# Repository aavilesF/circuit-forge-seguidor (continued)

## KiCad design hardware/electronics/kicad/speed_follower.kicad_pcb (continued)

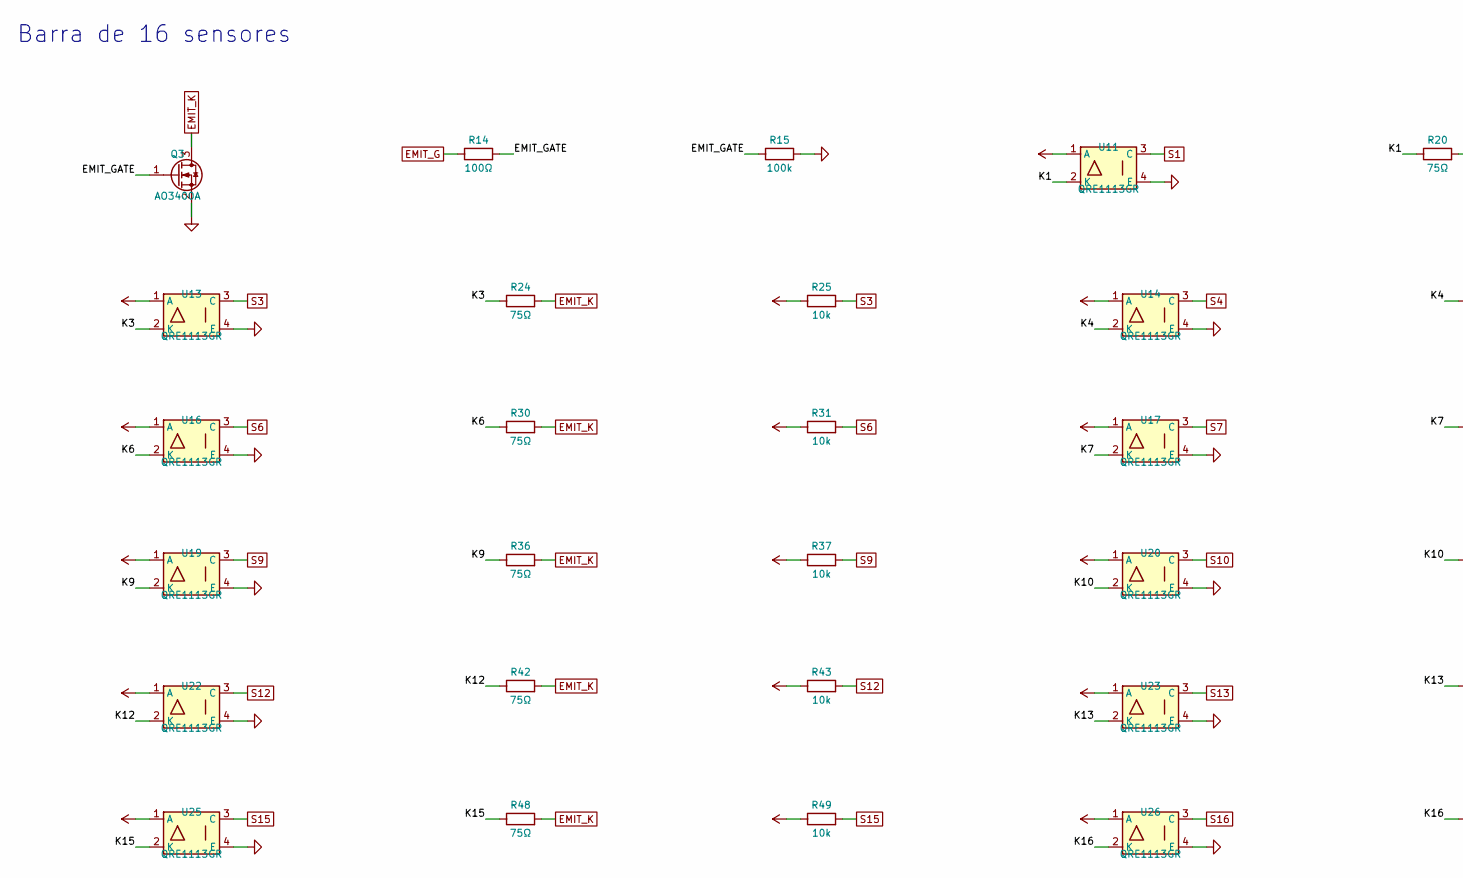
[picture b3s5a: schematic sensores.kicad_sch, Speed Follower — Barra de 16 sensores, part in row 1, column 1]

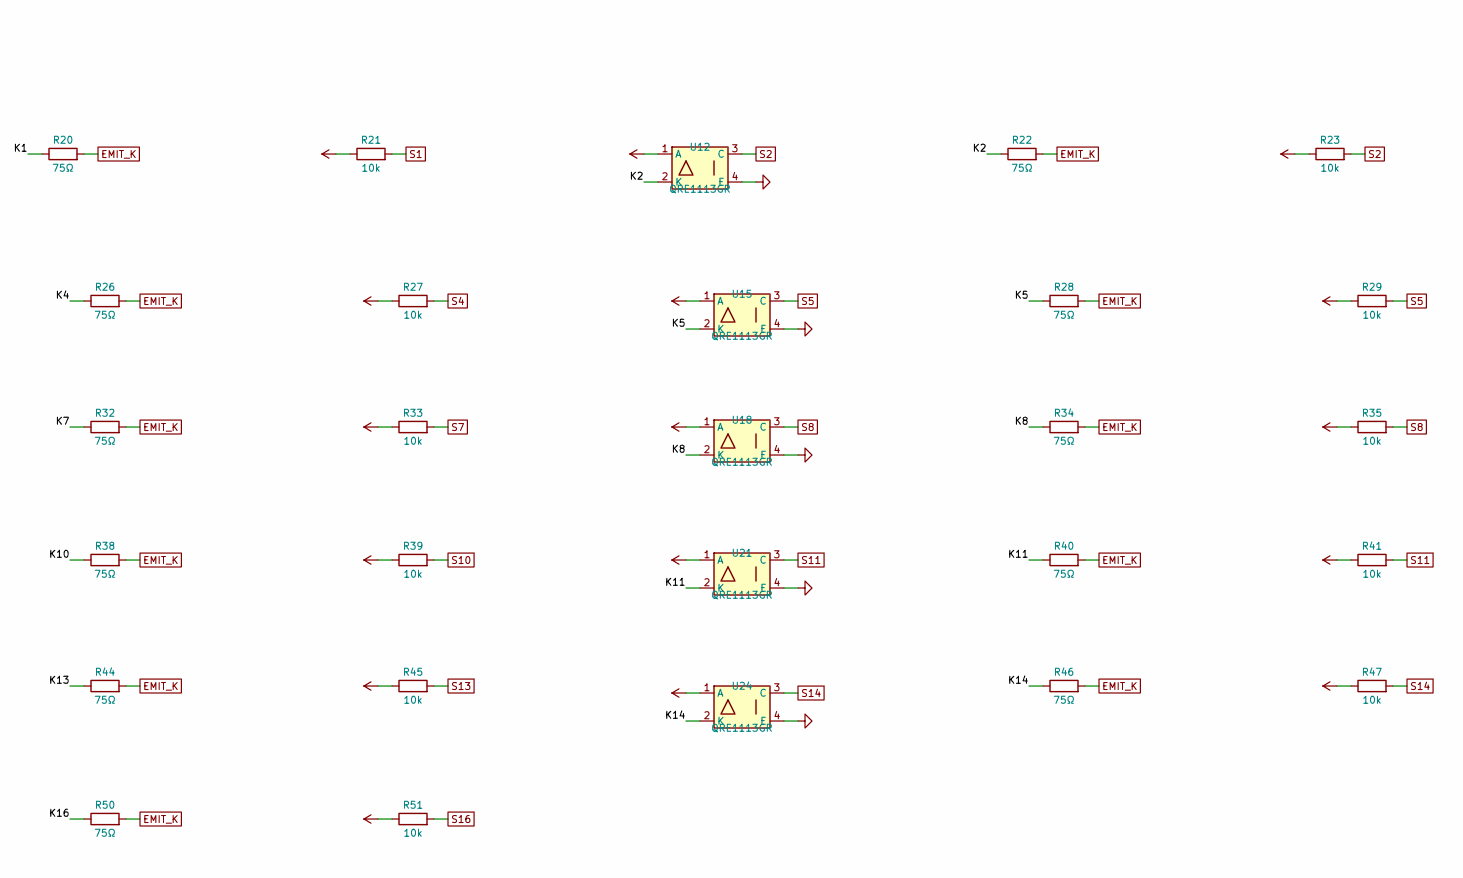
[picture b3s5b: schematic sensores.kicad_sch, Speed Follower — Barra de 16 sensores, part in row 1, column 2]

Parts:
Q3: AO3400A; SOT-23; MPN AO3400A
R14: 100Ω; R_0402_1005Metric; MPN RC0402FR-07100RL
R15: 100k; R_0402_1005Metric; MPN RC0402FR-07100KL
R20, R22, R24, R26, R28, R30, R32, R34, R36, R38, R40, R42, R44, R46, R48, R50: 75Ω; R_0603_1608Metric; MPN RC0603FR-0775RL
R21, R23, R25, R27, R29, R31, R33, R35, R37, R39, R41, R43, R45, R47, R49, R51: 10k; R_0402_1005Metric; MPN RC0402FR-0710KL
U11, U12, U13, U14, U15, U16, U17, U18, U19, U20, U21, U22, U23, U24, U25, U26: QRE1113GR; OnSemi_CASE100CY; MPN QRE1113GR

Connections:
+3V3: R21.1, R23.1, R25.1, R27.1, R29.1, R31.1, R33.1, R35.1, R37.1, R39.1, R41.1, R43.1, R45.1, R47.1, R49.1, R51.1, U11.1 (A), U12.1 (A), U13.1 (A), U14.1 (A), U15.1 (A), U16.1 (A), U17.1 (A), U18.1 (A), U19.1 (A), U20.1 (A), U21.1 (A), U22.1 (A), U23.1 (A), U24.1 (A), U25.1 (A), U26.1 (A); also elsewhere on the board
/Barra de 16 sensores/EMIT_GATE: Q3.1 (G), R14.2, R15.1
/Barra de 16 sensores/K1: R20.1, U11.2 (K)
/Barra de 16 sensores/K2: R22.1, U12.2 (K)
/Barra de 16 sensores/K3: R24.1, U13.2 (K)
/Barra de 16 sensores/K4: R26.1, U14.2 (K)
/Barra de 16 sensores/K5: R28.1, U15.2 (K)
/Barra de 16 sensores/K6: R30.1, U16.2 (K)
/Barra de 16 sensores/K7: R32.1, U17.2 (K)
/Barra de 16 sensores/K8: R34.1, U18.2 (K)
/Barra de 16 sensores/K9: R36.1, U19.2 (K)
/Barra de 16 sensores/K10: R38.1, U20.2 (K)
/Barra de 16 sensores/K11: R40.1, U21.2 (K)
/Barra de 16 sensores/K12: R42.1, U22.2 (K)
/Barra de 16 sensores/K13: R44.1, U23.2 (K)
/Barra de 16 sensores/K14: R46.1, U24.2 (K)
/Barra de 16 sensores/K15: R48.1, U25.2 (K)
/Barra de 16 sensores/K16: R50.1, U26.2 (K)
EMIT_G: R14.1; also elsewhere on the board
EMIT_K: Q3.3 (D), R20.2, R22.2, R24.2, R26.2, R28.2, R30.2, R32.2, R34.2, R36.2, R38.2, R40.2, R42.2, R44.2, R46.2, R48.2, R50.2; also elsewhere on the board
GND: Q3.2 (S), R15.2, U11.4 (E), U12.4 (E), U13.4 (E), U14.4 (E), U15.4 (E), U16.4 (E), U17.4 (E), U18.4 (E), U19.4 (E), U20.4 (E), U21.4 (E), U22.4 (E), U23.4 (E), U24.4 (E), U25.4 (E), U26.4 (E); also elsewhere on the board
S1: R21.2, U11.3 (C); also elsewhere on the board
S2: R23.2, U12.3 (C); also elsewhere on the board
S3: R25.2, U13.3 (C); also elsewhere on the board
S4: R27.2, U14.3 (C); also elsewhere on the board
S5: R29.2, U15.3 (C); also elsewhere on the board
S6: R31.2, U16.3 (C); also elsewhere on the board
S7: R33.2, U17.3 (C); also elsewhere on the board
S8: R35.2, U18.3 (C); also elsewhere on the board
S9: R37.2, U19.3 (C); also elsewhere on the board
S10: R39.2, U20.3 (C); also elsewhere on the board
S11: R41.2, U21.3 (C); also elsewhere on the board
S12: R43.2, U22.3 (C); also elsewhere on the board
S13: R45.2, U23.3 (C); also elsewhere on the board
S14: R47.2, U24.3 (C); also elsewhere on the board
S15: R49.2, U25.3 (C); also elsewhere on the board
S16: R51.2, U26.3 (C); also elsewhere on the board

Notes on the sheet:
Barra de 16 sensores

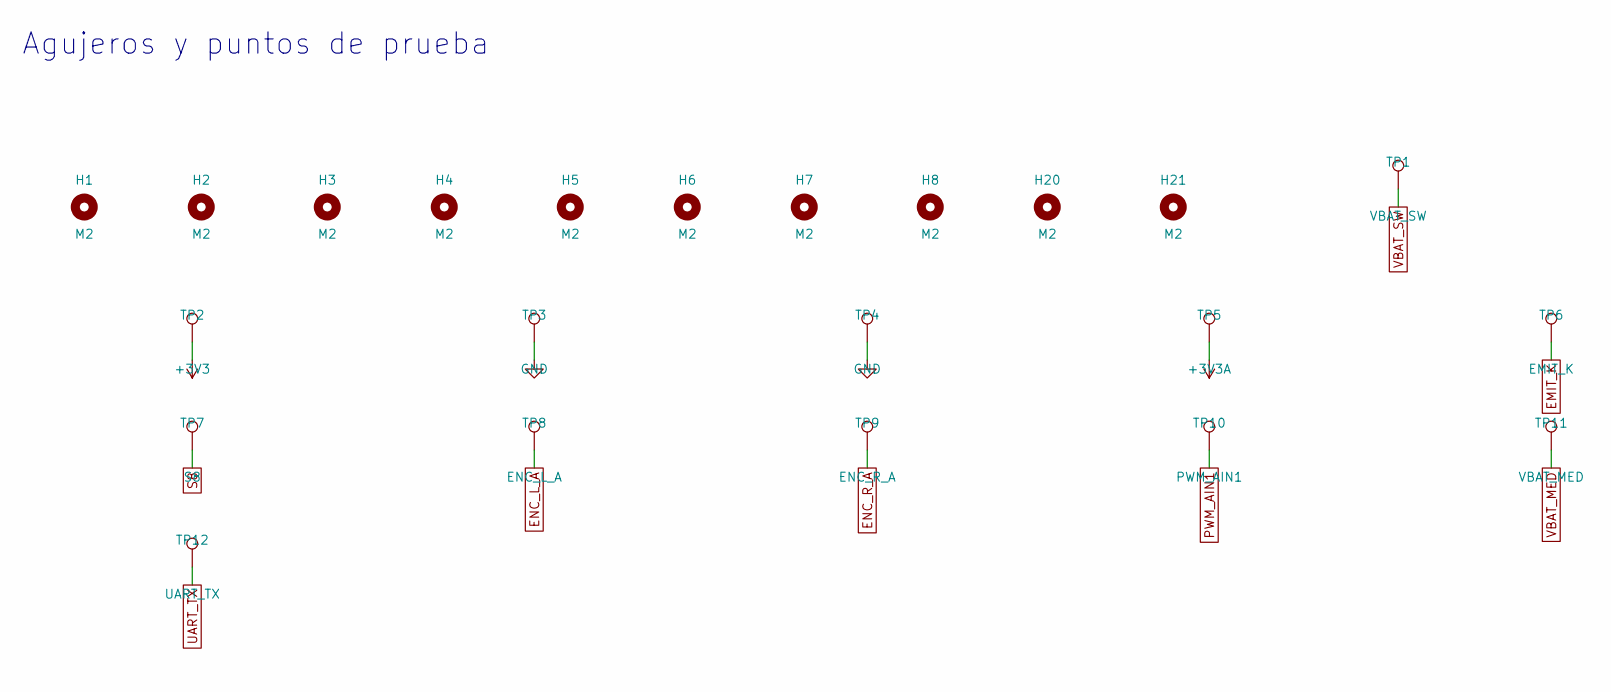
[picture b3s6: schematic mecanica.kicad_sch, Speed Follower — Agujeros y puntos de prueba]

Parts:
H1, H2, H3, H4, H5, H6, H7, H8, H20, H21: M2; MountingHole_2.2mm_M2; MPN —
TP1: VBAT_SW; TestPoint_Pad_D1.0mm; MPN —
TP2: +3V3; TestPoint_Pad_D1.0mm; MPN —
TP3, TP4: GND; TestPoint_Pad_D1.0mm; MPN —
TP5: +3V3A; TestPoint_Pad_D1.0mm; MPN —
TP6: EMIT_K; TestPoint_Pad_D1.0mm; MPN —
TP7: S8; TestPoint_Pad_D1.0mm; MPN —
TP8: ENC_L_A; TestPoint_Pad_D1.0mm; MPN —
TP9: ENC_R_A; TestPoint_Pad_D1.0mm; MPN —
TP10: PWM_AIN1; TestPoint_Pad_D1.0mm; MPN —
TP11: VBAT_MED; TestPoint_Pad_D1.0mm; MPN —
TP12: UART_TX; TestPoint_Pad_D1.0mm; MPN —

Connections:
+3V3: TP2.1; also elsewhere on the board
+3V3A: TP5.1; also elsewhere on the board
EMIT_K: TP6.1; also elsewhere on the board
ENC_L_A: TP8.1; also elsewhere on the board
ENC_R_A: TP9.1; also elsewhere on the board
GND: TP3.1, TP4.1; also elsewhere on the board
PWM_AIN1: TP10.1; also elsewhere on the board
S8: TP7.1; also elsewhere on the board
UART_TX: TP12.1; also elsewhere on the board
VBAT_MED: TP11.1; also elsewhere on the board
VBAT_SW: TP1.1; also elsewhere on the board

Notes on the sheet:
Agujeros y puntos de prueba

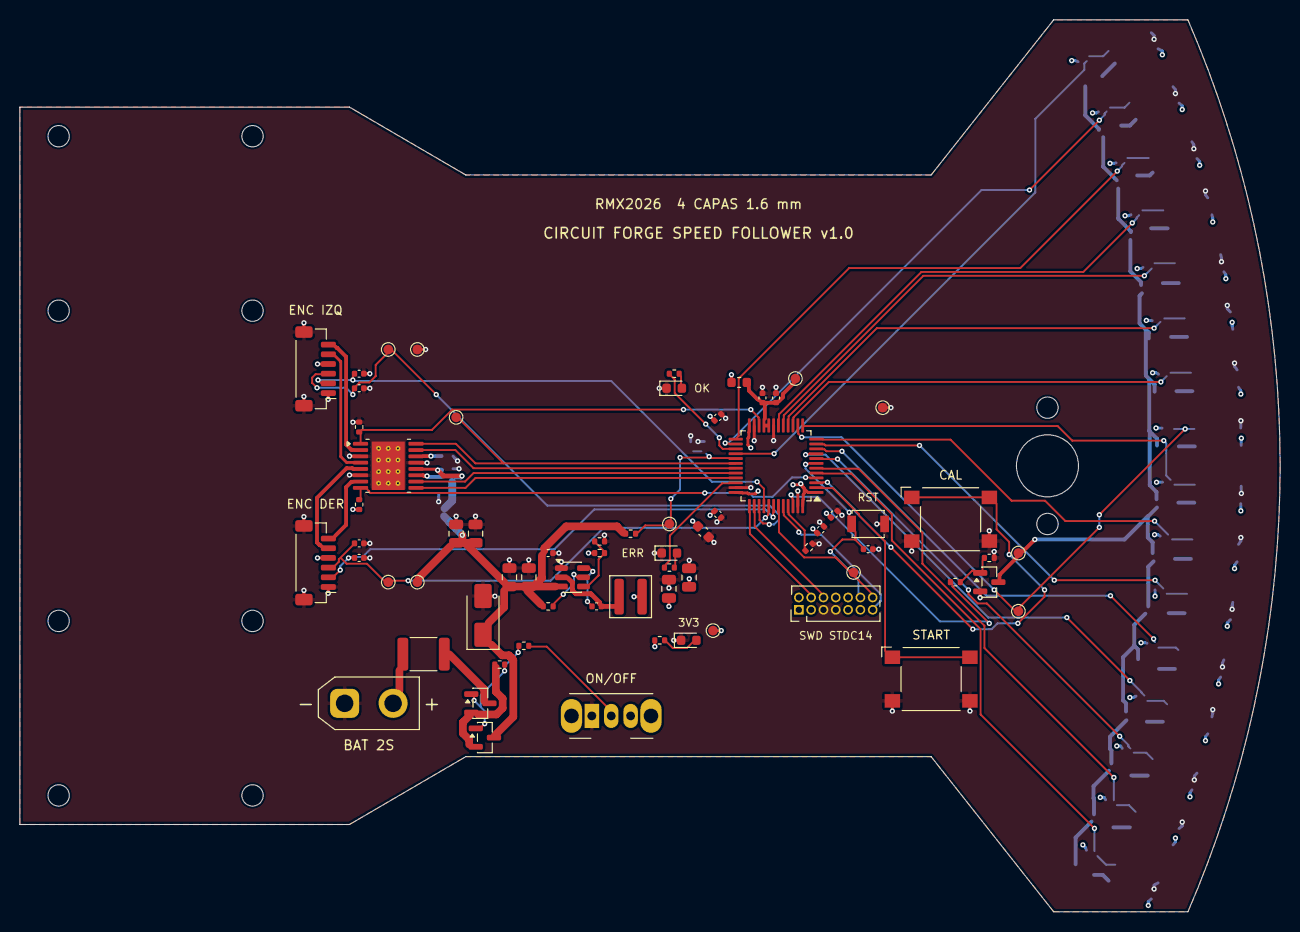
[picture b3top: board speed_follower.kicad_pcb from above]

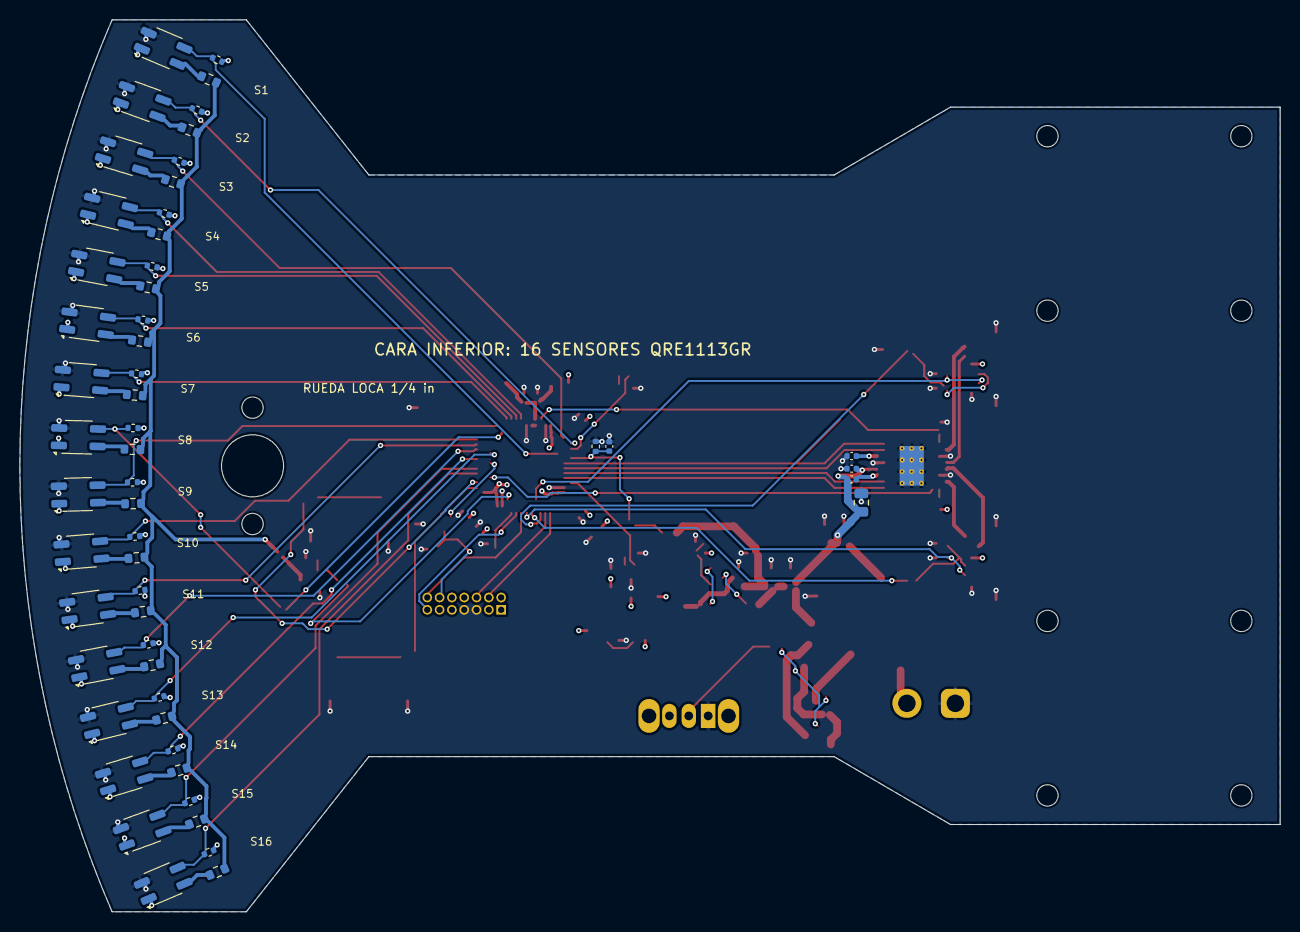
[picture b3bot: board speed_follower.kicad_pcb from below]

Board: 4 copper layers, 130.0 x 92.0 mm, 131 parts (54 on the bottom side), 78 nets.

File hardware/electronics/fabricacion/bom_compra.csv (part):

categoria,fabricante,modelo,numero_parte,descripcion,cantidad,tension,corriente,dimensiones,masa_unitaria_g,encapsulado,footprint,funcion,datasheet,observaciones_montaje,referencias,lado,verificado
A,Changzhou Amass Electronics,XT30UPB-M,XT30UPB-M,"Conector de batería XT30 macho vertical para PCB, 15 A (pin 1 −, pin 2 +)",1,500 V,15 A (30 A pico),10.2 × 5.2 × 8 mm (APROX),1.5,THT vertical,Connector_AMASS:AMASS_XT30UPB-M_1x02_P5.0mm_Vertical,Conector de batería (macho),https://www.tme.eu/Document/e5863b891432488e7531b3c4468225ac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,Verificar que el paquete Tattu traiga XT30 hembra (XT30U-F) antes de soldar,J1,superior,lcsc.com C428721; huella oficial KiCad AMASS
A,Littelfuse,1.5A/12V,1812L150/12DR,"Fusible reajustable PTC 1812, Ihold 1.5 A, 12 V",1,12 V máx,Ihold 1.5 A,4.5 × 3.2 mm,0.05,1812,Fuse:Fuse_1812_4532Metric,Fusible reajustable de la batería,https://www.littelfuse.com/assetdocs/littelfuse-ptc-1812l-datasheet,,F1,superior,digikey.com 1812L150-12DR
A,Alpha & Omega Semiconductor,AO3401A,AO3401A,MOSFET P −30 V −4 A SOT-23 (protección contra inversión),2,"VDS −30 V, VGS ±12 V",−4 A,2.9 × 1.3 × 1.1 mm,0.008,SOT-23,Package_TO_SOT_SMD:SOT-23,MOSFET P: inversión de polaridad y encendido,https://www.aosmd.com/res/datasheets/AO3401A.pdf,Q1 y Q2 espalda con espalda (fuentes unidas),Q1 Q2,superior,aosmd.com / distribuidores
A,YAGEO,100k,RC0402FR-07100KL,Resistencia 100kΩ 1 % 0402,5,50 V,1/16 W,1.0 × 0.5 mm,0.0006,0402,Resistor_SMD:R_0402_1005Metric,Resistencia,https://www.yageo.com/upload/media/product/productsearch/dat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,,R1 R3 R5 R13 R15,superior,nomenclatura de catálogo YAGEO RC (RC0402FR-07xxxL / RC0603FR-07xxxL)
A,YAGEO,10k,RC0402FR-0710KL,Resistencia 10kΩ 1 % 0402,20,50 V,1/16 W,1.0 × 0.5 mm,0.0006,0402,Resistor_SMD:R_0402_1005Metric,Resistencia,https://www.yageo.com/upload/media/product/productsearch/dat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,,R2 R7 R9 R12 R21 R23 R25 R27 R29 R31 R33 R35 R37 R39 R41 R43 R45 R47 R49 R51,inferior / superior,nomenclatura de catálogo YAGEO RC (RC0402FR-07xxxL / RC0603FR-07xxxL)
A,C&K,ENCENDIDO,OS102011MA1QN1,"Interruptor deslizante SPDT de ángulo recto, 100 mA 12 V (solo conmuta la compuerta)",1,12 V DC,100 mA,8.6 × 4.4 mm (cuerpo),0.5,THT ángulo recto,Button_Switch_THT:SW_Slide_SPDT_Angled_CK_OS102011MA1Q,Interruptor de encendido (conmuta la compuerta de Q1/Q2),https://www.ckswitches.com/media/1428/os.pdf,Actuador hacia el borde derecho,SW1,superior,rs-online 7874855; digikey OS102011MA1QN1
A,Littelfuse,SMAJ9.0A,SMAJ9.0A,"TVS unidireccional 400 W, 9.0 V de trabajo (DO-214AC)",1,"VRWM 9.0 V, Vc 15.4 V",26 A pico,4.3 × 2.6 × 2.2 mm,0.07,DO-214AC (SMA),Diode_SMD:D_SMA,TVS de la alimentación del motor,https://www.littelfuse.com/assetdocs/littelfuse-tvs-diode-sm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,Cátodo (banda) hacia VBAT_SW,D1,superior,digikey.com SMAJ9-0A (Littelfuse)
A,Murata,22µF,GRM21BR61E226ME44L,Condensador cerámico 22µF 25 V X5R 0805,4,25 V,,2.0 × 1.25 mm,0.008,0805,Capacitor_SMD:C_0805_2012Metric,Condensador,https://www.murata.com/en-us/products/capacitor/ceramiccapacitor,,C1 C2 C8 C9,superior,distribuidores (Murata GRM)
A,YAGEO,33k,RC0402FR-0733KL,Resistencia 33kΩ 1 % 0402,1,50 V,1/16 W,1.0 × 0.5 mm,0.0006,0402,Resistor_SMD:R_0402_1005Metric,Resistencia,https://www.yageo.com/upload/media/product/productsearch/dat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,,R4,inferior,nomenclatura de catálogo YAGEO RC (RC0402FR-07xxxL / RC0603FR-07xxxL)
A,Murata,100nF,GRM155R71C104KA88D,Condensador cerámico 100nF 16 V X7R 0402,10,16 V,,1.0 × 0.5 mm,0.0006,0402,Capacitor_SMD:C_0402_1005Metric,Condensador,https://www.murata.com/en-us/products/capacitor/ceramiccapacitor,,C3 C6 C7 C10 C11 C12 C13 C16 C17 C21,inferior / superior,distribuidores (Murata GRM)
A,Texas Instruments,TPS563200,TPS563200DDCR,"Convertidor reductor síncrono 4.5-17 V, 3 A, 650 kHz (SOT-23-6)",1,VIN 4.5-17 V,3 A,2.9 × 1.6 × 1.1 mm,0.02,SOT-23-6,Package_TO_SOT_SMD:SOT-23-6,Reductor 3.3 V,https://www.ti.com/lit/ds/symlink/tps563200.pdf,R6/R7 fijan 3.30 V (VFB 0.765 V),U2,superior,pines y tabla de componentes: hoja de datos TI (chipdip.ru DOC003725965)
A,Murata,10µF,GRM21BR61E106KA73L,Condensador cerámico 10µF 25 V X5R 0805,3,25 V,,2.0 × 1.25 mm,0.008,0805,Capacitor_SMD:C_0805_2012Metric,Condensador,https://www.murata.com/en-us/products/capacitor/ceramiccapacitor,,C4 C5 C20,inferior / superior,distribuidores (Murata GRM)
A,Würth Elektronik,2.2µH,74438357022,"Inductor blindado WE-MAPI 4030, 2.2 µH, IR 7.1 A, Isat 9.2 A, 26 mΩ",1,—,"IR 7.1 A, Isat 9.2 A",4.1 × 4.1 × 3.1 mm,0.25,WE-MAPI 4030,Inductor_SMD:L_Wuerth_MAPI-4030,Inductor del reductor,https://www.we-online.com/components/products/datasheet/7443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,,L1,superior,"digikey.com / flux.ai (WE-MAPI 4030, 2.2 µH, 26 mΩ)"
A,YAGEO,33.2k,RC0402FR-0733K2L,Resistencia 33.2kΩ 1 % 0402,1,50 V,1/16 W,1.0 × 0.5 mm,0.0006,0402,Resistor_SMD:R_0402_1005Metric,Resistencia,https://www.yageo.com/upload/media/product/productsearch/dat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,,R6,superior,nomenclatura de catálogo YAGEO RC (RC0402FR-07xxxL / RC0603FR-07xxxL)
A,Kingbright,PWR,APT1608SGC,LED verde 0603 (3.3 V presente),2,VF ≈ 2.2 V,20 mA máx,1.6 × 0.8 mm,0.002,0603,LED_SMD:LED_0603_1608Metric,LED verde (3.3 V y estado),https://www.kingbrightusa.com/images/catalog/SPEC/APT1608SGC.pdf,Cátodo: marca verde/raya de la huella,D2 D3,superior,digikey APT1608SGC (Kingbright)
A,YAGEO,1k,RC0402FR-071KL,Resistencia 1kΩ 1 % 0402,3,50 V,1/16 W,1.0 × 0.5 mm,0.0006,0402,Resistor_SMD:R_0402_1005Metric,Resistencia,https://www.yageo.com/upload/media/product/productsearch/dat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,,R8 R10 R11,superior,nomenclatura de catálogo YAGEO RC (RC0402FR-07xxxL / RC0603FR-07xxxL)
A,STMicroelectronics,STM32G431CBT6,STM32G431CBT6,"MCU Arm Cortex-M4F 170 MHz, 128 KB flash, 32 KB RAM, 2 ADC 12 bits, LQFP-48",1,1.71-3.6 V,≈ 30 mA a 170 MHz,7 × 7 × 1.4 mm,0.2,LQFP-48,Package_QFP:LQFP-48_7x7mm_P0.5mm,"Microcontrolador (control, ADC, PWM, encoders)",https://www.st.com/resource/en/datasheet/stm32g431cb.pdf,"Pin 1 marcado en la serigrafía; soldar con flux, revisar puentes entre pines",U1,superior,ficha y pines: st.com; funciones alternas: STM32_open_pin_data (ST)
A,Murata,4.7µF,GRM188R61A475KE15D,Condensador cerámico 4.7µF 10 V X5R 0603,1,10 V,,1.6 × 0.8 mm,0.002,0603,Capacitor_SMD:C_0603_1608Metric,Condensador,https://www.murata.com/en-us/products/capacitor/ceramiccapacitor,,C14,superior,distribuidores (Murata GRM)
A,Murata,220Ω@100MHz,BLM18PG221SN1D,"Ferrita 220 Ω a 100 MHz, 1.4 A, 0603 (filtro de VDDA)",1,—,1.4 A,1.6 × 0.8 × 0.8 mm,0.003,0603,Inductor_SMD:L_0603_1608Metric,Ferrita de VDDA,https://www.murata.com/en-us/products/productdetail?partno=B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,,FB1,superior,digikey.com / rs-online
A,Murata,1µF,GRM155R61A105KE15D,Condensador cerámico 1µF 10 V X5R 0402,1,10 V,,1.0 × 0.5 mm,0.0006,0402,Capacitor_SMD:C_0402_1005Metric,Condensador,https://www.murata.com/en-us/products/capacitor/ceramiccapacitor,,C15,superior,distribuidores (Murata GRM)
A,Omron,RESET,B3U-1000P,Pulsador táctil SMD 3.0 × 2.5 mm (reinicio),1,12 V DC,50 mA,3.0 × 2.5 × 1.6 mm,0.03,SMD,Button_Switch_SMD:SW_SPST_B3U-1000P,Botón RESET,https://omronfs.omron.com/en_US/ecb/products/pdf/en-b3u.pdf,,SW4,superior,lcsc C231329; omron.com
A,Omron,START,B3FS-1000P,"Pulsador táctil SMD 6 × 6 × 3.1 mm (arranque, regla R08)",2,24 V DC,50 mA,6 × 6 × 3.1 mm,0.25,SMD,Button_Switch_SMD:SW_SPST_Omron_B3FS-100xP,Botones START y CAL,https://omronfs.omron.com/en_US/ecb/products/pdf/en-b3fs.pdf,,SW2 SW3,superior,lcsc C271750; omron.com
A,Kingbright,ERR,APT1608EC,LED rojo 0603 (falla / batería baja),1,VF ≈ 2.0 V,20 mA máx,1.6 × 0.8 mm,0.002,0603,LED_SMD:LED_0603_1608Metric,LED rojo (falla),https://www.kingbrightusa.com/images/catalog/SPEC/APT1608SGC.pdf,,D4,superior,digikey APT1608EC (Kingbright)
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
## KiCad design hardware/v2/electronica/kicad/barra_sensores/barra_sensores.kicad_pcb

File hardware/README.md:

# Hardware — Speed Follower (configuración definitiva)

| Carpeta | Contenido | Detalle |
|---|---|---|
| [`electronics/`](electronics/README.md) | Proyecto KiCad 9 (esquemático jerárquico y PCB-chasis de 4 capas ruteada), generadores, verificaciones ERC/DRC/paridad, paquete de fabricación y vistas 2D/3D de la PCBA | [`electronics/README.md`](electronics/README.md), [`electronics/fabricacion/LEEME.md`](electronics/fabricacion/LEEME.md) |
| [`mechanical/`](mechanical/README.md) | CAD del robot completo (CadQuery): piezas impresas en STEP/STL, planos, ensamble STEP, vistas, verificación de interferencias, caja, altura, masa y CG | [`mechanical/README.md`](mechanical/README.md), [`mechanical/VERIFICACION_MECANICA.md`](mechanical/VERIFICACION_MECANICA.md) |
| `geometria.py` | Geometría única del robot (contorno de la PCB, arco y posición de los sensores, soportes, rueda loca, alturas) calculada desde `config/robot_maestro.yaml`; la usan la PCB, el CAD y las verificaciones | — |

Arquitectura y justificación: [`docs/ARQUITECTURA.md`](../docs/ARQUITECTURA.md). Lista de compra: [`docs/BOM_FINAL.csv`](../docs/BOM_FINAL.csv).
Montaje, pruebas de aceptación y calibración: [`docs/MANUAL_ENSAMBLAJE.md`](../docs/MANUAL_ENSAMBLAJE.md).

Todo lo que contiene esta carpeta está verificado en **EDA y CAD**; no hay placa ni robot fabricados.

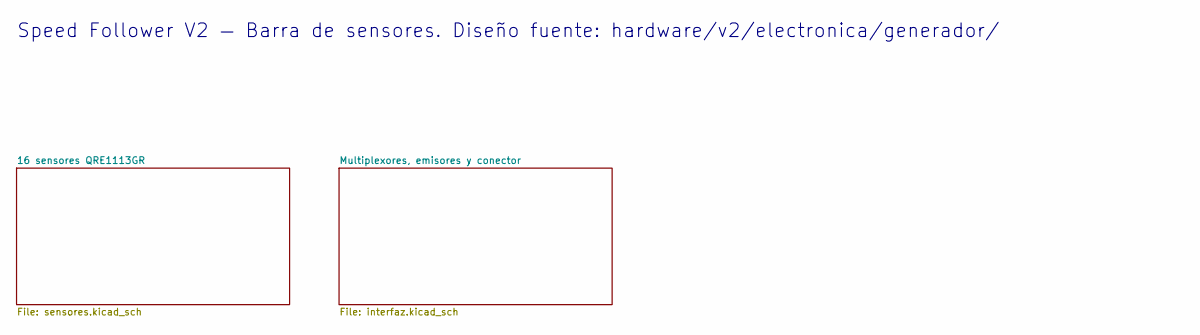
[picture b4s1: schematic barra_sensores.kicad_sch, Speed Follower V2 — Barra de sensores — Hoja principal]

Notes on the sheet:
Speed Follower V2 — Barra de sensores. Diseño fuente: hardware/v2/electronica/generador/

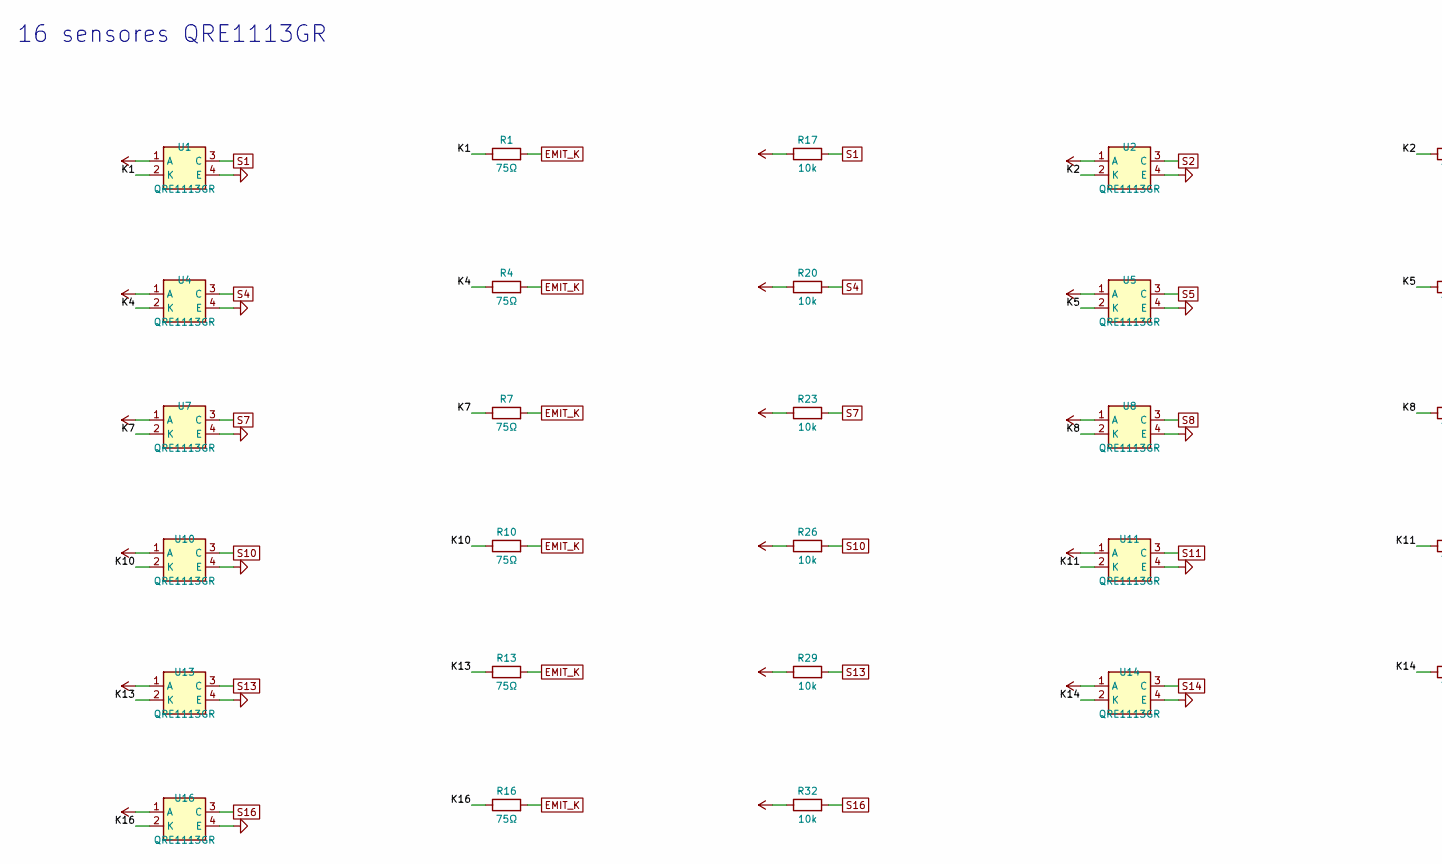
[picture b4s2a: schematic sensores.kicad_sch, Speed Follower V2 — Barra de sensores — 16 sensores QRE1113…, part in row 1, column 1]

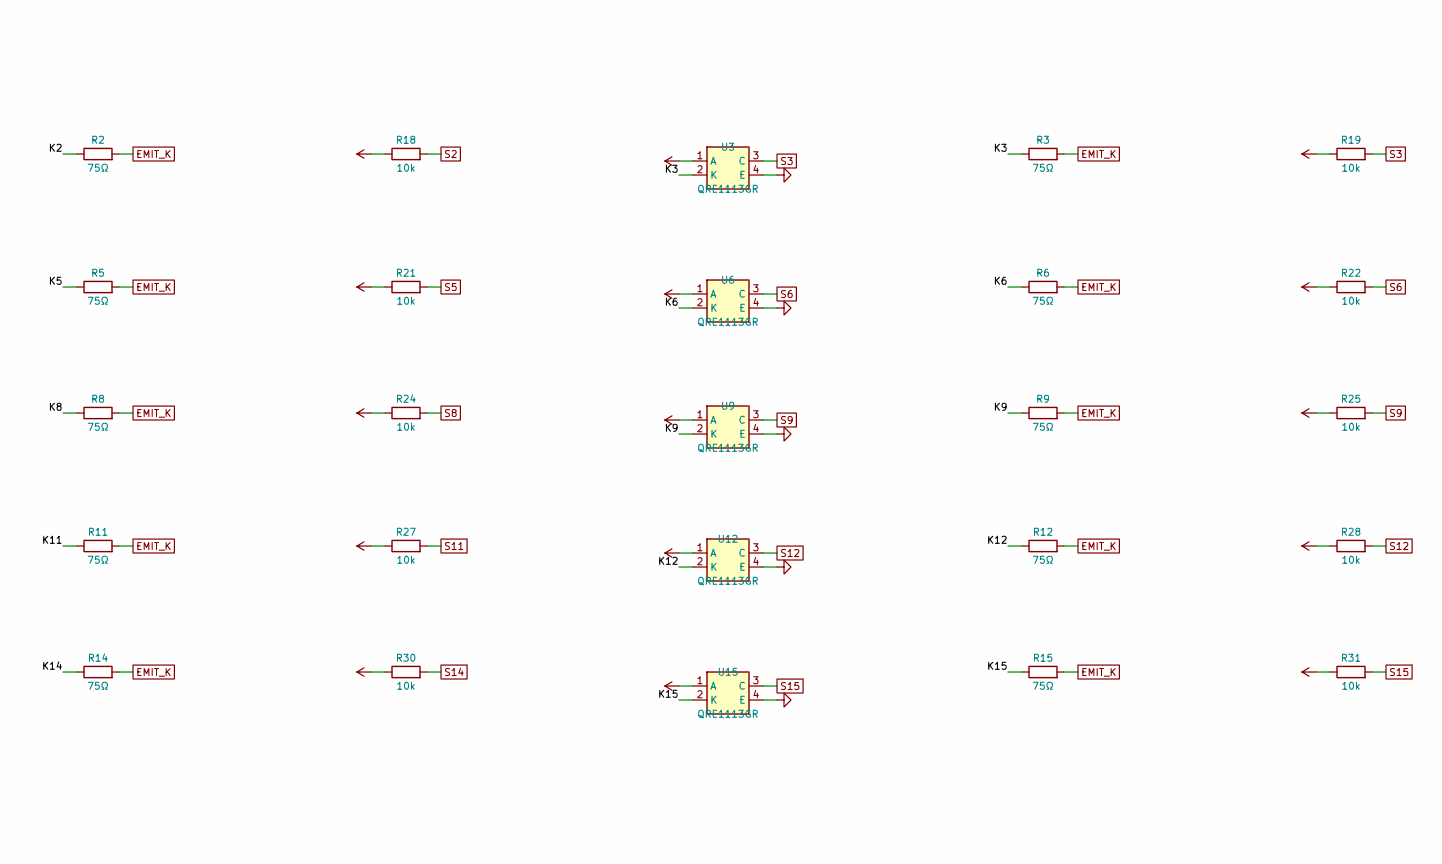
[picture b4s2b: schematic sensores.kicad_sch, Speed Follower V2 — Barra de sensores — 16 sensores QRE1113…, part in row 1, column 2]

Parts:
R1, R2, R3, R4, R5, R6, R7, R8, R9, R10, R11, R12, R13, R14, R15, R16: 75Ω; R_0603_1608Metric; MPN RC0603FR-0775RL
R17, R18, R19, R20, R21, R22, R23, R24, R25, R26, R27, R28, R29, R30, R31, R32: 10k; R_0402_1005Metric; MPN RC0402FR-0710KL
U1, U2, U3, U4, U5, U6, U7, U8, U9, U10, U11, U12, U13, U14, U15, U16: QRE1113GR; OnSemi_CASE100CY; MPN QRE1113GR

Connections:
+3V3: R17.1, R18.1, R19.1, R20.1, R21.1, R22.1, R23.1, R24.1, R25.1, R26.1, R27.1, R28.1, R29.1, R30.1, R31.1, R32.1, U1.1 (A), U2.1 (A), U3.1 (A), U4.1 (A), U5.1 (A), U6.1 (A), U7.1 (A), U8.1 (A), U9.1 (A), U10.1 (A), U11.1 (A), U12.1 (A), U13.1 (A), U14.1 (A), U15.1 (A), U16.1 (A); also elsewhere on the board
/16 sensores QRE1113GR/K1: R1.1, U1.2 (K)
/16 sensores QRE1113GR/K2: R2.1, U2.2 (K)
/16 sensores QRE1113GR/K3: R3.1, U3.2 (K)
/16 sensores QRE1113GR/K4: R4.1, U4.2 (K)
/16 sensores QRE1113GR/K5: R5.1, U5.2 (K)
/16 sensores QRE1113GR/K6: R6.1, U6.2 (K)
/16 sensores QRE1113GR/K7: R7.1, U7.2 (K)
/16 sensores QRE1113GR/K8: R8.1, U8.2 (K)
/16 sensores QRE1113GR/K9: R9.1, U9.2 (K)
/16 sensores QRE1113GR/K10: R10.1, U10.2 (K)
/16 sensores QRE1113GR/K11: R11.1, U11.2 (K)
/16 sensores QRE1113GR/K12: R12.1, U12.2 (K)
/16 sensores QRE1113GR/K13: R13.1, U13.2 (K)
/16 sensores QRE1113GR/K14: R14.1, U14.2 (K)
/16 sensores QRE1113GR/K15: R15.1, U15.2 (K)
/16 sensores QRE1113GR/K16: R16.1, U16.2 (K)
EMIT_K: R1.2, R2.2, R3.2, R4.2, R5.2, R6.2, R7.2, R8.2, R9.2, R10.2, R11.2, R12.2, R13.2, R14.2, R15.2, R16.2; also elsewhere on the board
GND: U1.4 (E), U2.4 (E), U3.4 (E), U4.4 (E), U5.4 (E), U6.4 (E), U7.4 (E), U8.4 (E), U9.4 (E), U10.4 (E), U11.4 (E), U12.4 (E), U13.4 (E), U14.4 (E), U15.4 (E), U16.4 (E); also elsewhere on the board
S1: R17.2, U1.3 (C); also elsewhere on the board
S2: R18.2, U2.3 (C); also elsewhere on the board
S3: R19.2, U3.3 (C); also elsewhere on the board
S4: R20.2, U4.3 (C); also elsewhere on the board
S5: R21.2, U5.3 (C); also elsewhere on the board
S6: R22.2, U6.3 (C); also elsewhere on the board
S7: R23.2, U7.3 (C); also elsewhere on the board
S8: R24.2, U8.3 (C); also elsewhere on the board
S9: R25.2, U9.3 (C); also elsewhere on the board
S10: R26.2, U10.3 (C); also elsewhere on the board
S11: R27.2, U11.3 (C); also elsewhere on the board
S12: R28.2, U12.3 (C); also elsewhere on the board
S13: R29.2, U13.3 (C); also elsewhere on the board
S14: R30.2, U14.3 (C); also elsewhere on the board
S15: R31.2, U15.3 (C); also elsewhere on the board
S16: R32.2, U16.3 (C); also elsewhere on the board

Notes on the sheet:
16 sensores QRE1113GR

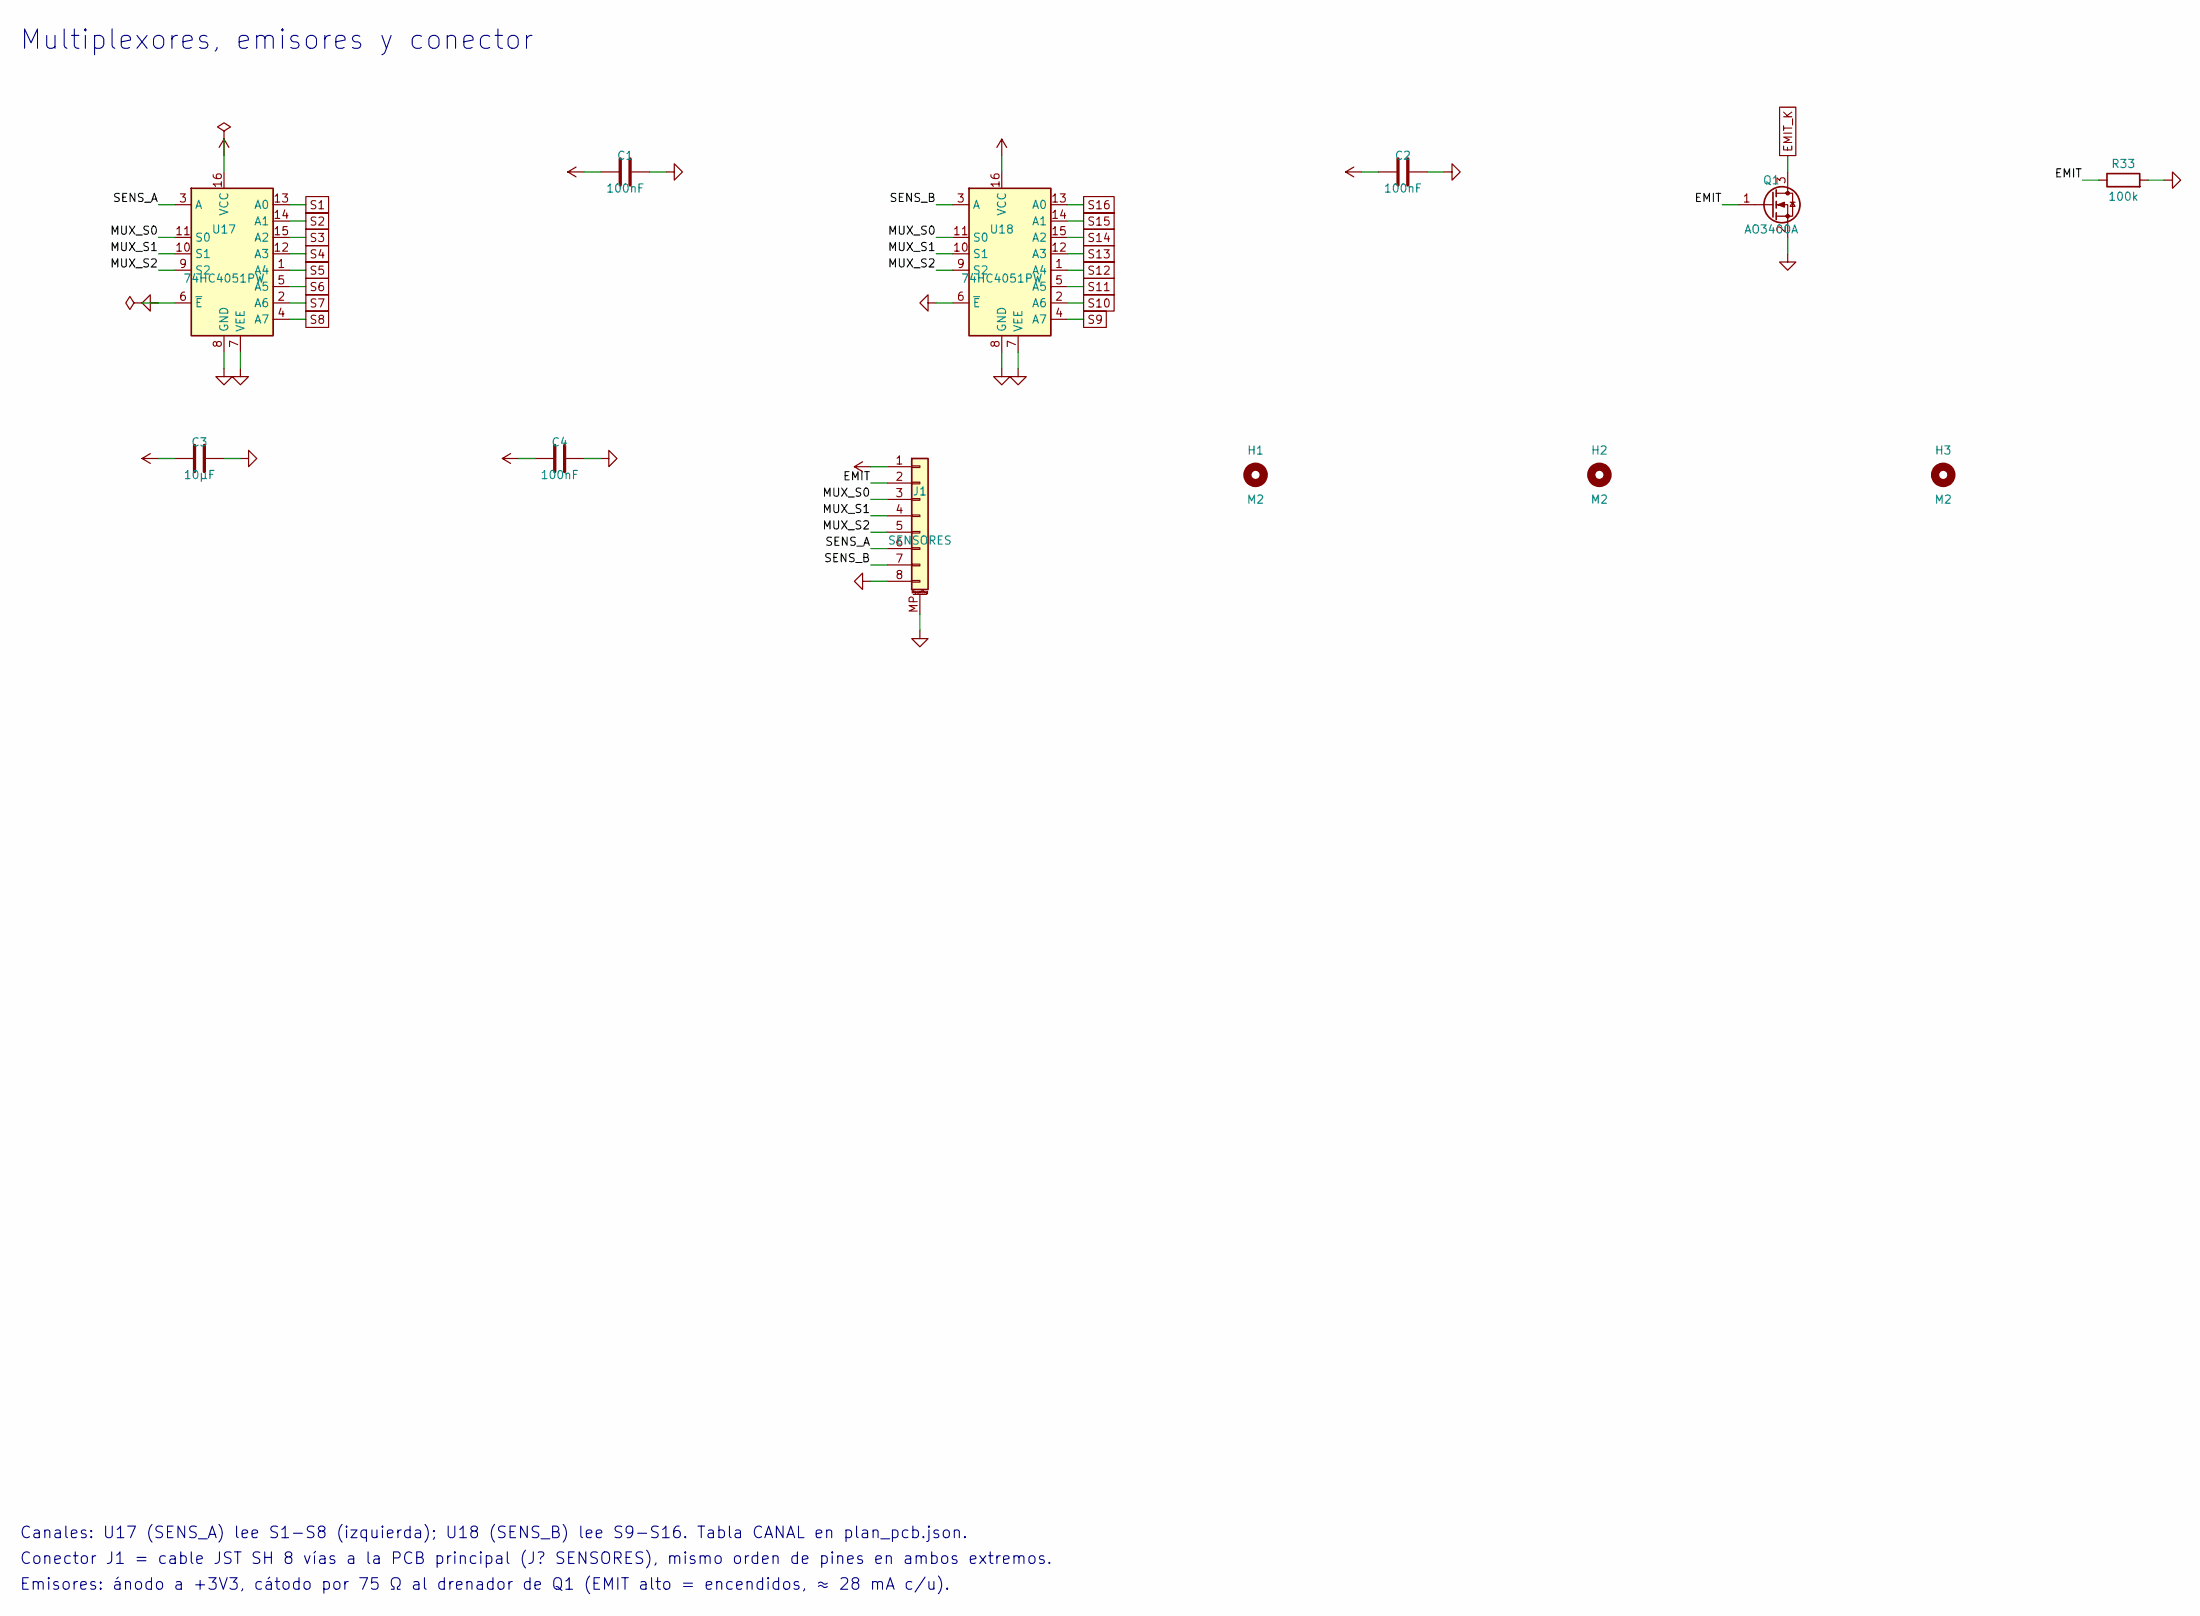
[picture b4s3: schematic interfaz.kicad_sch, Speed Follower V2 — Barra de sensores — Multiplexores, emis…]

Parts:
C1, C2, C4: 100nF; C_0402_1005Metric; MPN GRM155R71C104KA88D
C3: 10µF; C_0805_2012Metric; MPN GRM21BR61E106KA73L
H1, H2, H3: M2; MountingHole_2.2mm_M2; MPN —
J1: SENSORES; JST_SH_BM08B-SRSS-TB_1x08-1MP_P1.00mm_Vertical; MPN BM08B-SRSS-TB
Q1: AO3400A; SOT-23; MPN AO3400A
R33: 100k; R_0402_1005Metric; MPN RC0402FR-07100KL
U17, U18: 74HC4051PW; TSSOP-16_4.4x5mm_P0.65mm; MPN 74HC4051PW,118

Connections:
+3V3: C1.1, C2.1, C3.1, C4.1, J1.1, U17.16 (VCC), U18.16 (VCC); also elsewhere on the board
/Multiplexores, emisores y conector/EMIT: J1.2, Q1.1 (G), R33.1
/Multiplexores, emisores y conector/MUX_S0: J1.3, U17.11 (S0), U18.11 (S0)
/Multiplexores, emisores y conector/MUX_S1: J1.4, U17.10 (S1), U18.10 (S1)
/Multiplexores, emisores y conector/MUX_S2: J1.5, U17.9 (S2), U18.9 (S2)
/Multiplexores, emisores y conector/SENS_A: J1.6, U17.3 (A)
/Multiplexores, emisores y conector/SENS_B: J1.7, U18.3 (A)
EMIT_K: Q1.3 (D); also elsewhere on the board
GND: C1.2, C2.2, C3.2, C4.2, J1.8, J1.MP (MountPin), Q1.2 (S), R33.2, U17.6 (~E), U17.7 (VEE), U17.8 (GND), U18.6 (~E), U18.7 (VEE), U18.8 (GND); also elsewhere on the board
S1: U17.13 (A0); also elsewhere on the board
S2: U17.14 (A1); also elsewhere on the board
S3: U17.15 (A2); also elsewhere on the board
S4: U17.12 (A3); also elsewhere on the board
S5: U17.1 (A4); also elsewhere on the board
S6: U17.5 (A5); also elsewhere on the board
S7: U17.2 (A6); also elsewhere on the board
S8: U17.4 (A7); also elsewhere on the board
S9: U18.4 (A7); also elsewhere on the board
S10: U18.2 (A6); also elsewhere on the board
S11: U18.5 (A5); also elsewhere on the board
S12: U18.1 (A4); also elsewhere on the board
S13: U18.12 (A3); also elsewhere on the board
S14: U18.15 (A2); also elsewhere on the board
S15: U18.14 (A1); also elsewhere on the board
S16: U18.13 (A0); also elsewhere on the board

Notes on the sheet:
Multiplexores, emisores y conector
Canales: U17 (SENS_A) lee S1-S8 (izquierda); U18 (SENS_B) lee S9-S16. Tabla CANAL en plan_pcb.json.
Conector J1 = cable JST SH 8 vías a la PCB principal (J? SENSORES), mismo orden de pines en ambos extremos.
Emisores: ánodo a +3V3, cátodo por 75 Ω al drenador de Q1 (EMIT alto = encendidos, ≈ 28 mA c/u).
